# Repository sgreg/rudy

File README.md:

# RUDY - the Random USB Device

RUDY started out as a test and play-around device for USB development using the [Objective Development V-USB library](https://www.obdev.at/products/vusb/index.html), but also serves as standard ATmega328 development board.

## Links
- [Official Website](https://rudy.craplab.fi/)
- [Hackaday.io Project Page](https://hackaday.io/project/174101-rudy)

## Features

- breadboard-friendly prototyping board, taking up only one additional row on each side compared to a standalone ATmega328 microcontroller
- Arduino compatible [..ish](firmware/arduino/)
- USB port wired to the ATmega328 for out-of-the-box USB functionality via the V-USB library
- own, dedicated [USB VID/PID pair](http://pid.codes/1209/B00B/) thanks to [pid.codes](http://pid.codes/)
- USB-powered with additional 3.3V voltage regulator on board to select either 5.0 or 3.3V supply voltage
- clocked by 12.0 MHz crystal to comply with V-USB and also 3.3V supply voltage
- 6-pin ISP header for programming, with additional option to power the board directly from the programmer
- power-indicating LEDs mounted under the IC, shining in a mysterious glow (oh yeah)
- DIP28 ATmega328, allowing easy replacement if it ever gets fried (no no)
- fully open source and [certified as such](https://certification.oshwa.org/fi000002.html) by the [Open Source Hardware Association (OSHWA)](https://www.oshwa.org/)

<p align="center">

</p>

## Hardware

RUDY is primarily a hardware project, so all the design file for KiCad along with the schematic as PDF and Gerber files are found in the [`hardware/`](hardware/rudy/) directory. And if you want to go straight ahead and build your own board, [the PCB is available from OSH Park](https://oshpark.com/projects/RQf8bXd4).

As RUDY can theoretically function as an [USBasp programmer](https://www.fischl.de/usbasp/), there's also [an adapter board](hardware/usbasp-adapter) available - and is also [available from OSH Park](https://oshpark.com/projects/pueZ0qkO)

## Firmware

Again, RUDY is primarily a development board, and as such is there for _your_ firmware. But well, everything and everyone has to start somewhere, so the [`firmware/`](firmware/) directory has a (still-to-grow) collection of example projects, both using the V-USB library and using RUDY as regular, ATmega328 microcontroller board.

## License
RUDY is fully open source. All hardware files are released under the [CERN Open Hardware License v1.2](https://ohwr.org/project/licenses/wikis/cern-ohl-v1.2), all example source code is released under the [MIT License](https://choosealicense.com/licenses/mit/), and all documentation within this git repository is provided under the terms of a [Creative Commons Attribution 4.0 International (CC BY 4.0) license](https://creativecommons.org/licenses/by/4.0/).

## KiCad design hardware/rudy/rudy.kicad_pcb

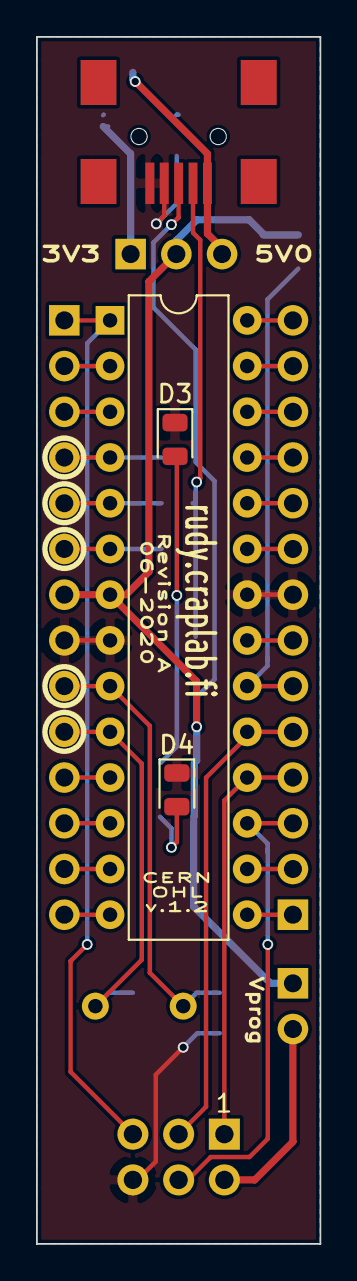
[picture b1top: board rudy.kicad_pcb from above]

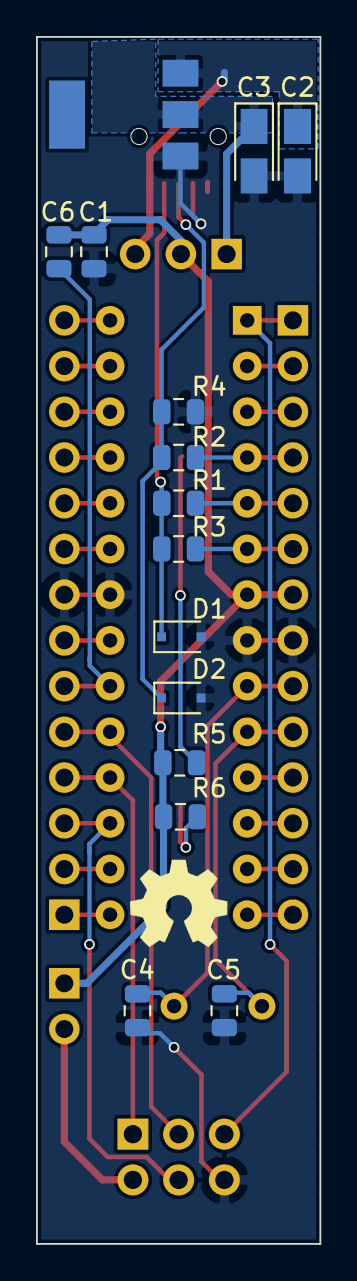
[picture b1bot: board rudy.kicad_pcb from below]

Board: 2 copper layers, 15.7 x 67.1 mm, 26 parts (16 on the bottom side), 34 nets.

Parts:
C1, C6: 100n; C_0805_2012Metric
C2, C3: 10u; CP_Tantalum_Case-A_EIA-3216-18_Reflow
C4, C5: 22p; C_0805_2012Metric
D1, D2: 3V6; D_SOD-323F
D3, D4: LED; LED_0805_2012Metric
IC1: ATMEGA328-P; DIP-28_W7.62mm
JP1: JUMPER3; Pin_Header_Straight_1x03_Pitch2.54mm
JP2: JUMPER; Pin_Header_Straight_1x02_Pitch2.54mm
P1: CONN1; Socket_Strip_Straight_1x14_Pitch2.54mm
P2: CONN2; Socket_Strip_Straight_1x14_Pitch2.54mm
P3: SERPROG; IDC_Header_Straight_6pins
P4: USB_B; USB_Mini-B
R1, R2: 68R; R_0805_2012Metric
R3: 1k5; R_0805_2012Metric
R4: 1M; R_0805_2012Metric
R5, R6: 120R; R_0805_2012Metric
U1: LD1117S33TR; SOT-223
Y1: Crystal; Crystal_HC49-U_Vertical
oshw: LOGO; oshw_50

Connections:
/#RESET: IC1.1, P1.1, P3.5
/AREF: IC1.21, P2.7
/AVCC: C6.2, IC1.20, P2.6
/PB0: IC1.14, P1.14
/PB1: IC1.15, P2.1
/PB2: IC1.16, P2.2
/PB3: IC1.17, P2.3, P3.4
/PB4: IC1.18, P2.4, P3.1
/PB5: IC1.19, P2.5, P3.3
/PB6: C4.1, IC1.9, P1.9, Y1.1
/PB7: C5.1, IC1.10, P1.10, Y1.2
/PC0: IC1.23, P2.9
/PC1: IC1.24, P2.10
/PC2: IC1.25, P2.11
/PC3: IC1.26, P2.12
/PC4: IC1.27, P2.13
/PC5: IC1.28, P2.14
/PD0: IC1.2, P1.2
/PD1: IC1.3, P1.3
/PD2: IC1.4, P1.4, R2.1
/PD3: IC1.5, P1.5, R1.1
/PD4: IC1.6, P1.6, R3.1
/PD5: IC1.11, P1.11
/PD6: IC1.12, P1.12
/PD7: IC1.13, P1.13
/VCC: C1.1, C6.1, IC1.7, JP1.2, JP2.1, P1.7, R5.2, R6.2
GND: C1.2, C2.2, C3.2, C4.2, C5.2, D1.2, D2.2, D3.1, D4.1, IC1.8, IC1.22, P1.8, P2.8, P3.6, P4.4, P4.5, R4.2, U1.1
unnamed: C2.1, JP1.3, P4.1, U1.3
unnamed: C3.1, JP1.1, U1.2
unnamed: D1.1, P4.2, R1.2, R3.2
unnamed: D2.1, P4.3, R2.2, R4.1
unnamed: D3.2, R5.1
unnamed: D4.2, R6.1
unnamed: JP2.2, P3.2

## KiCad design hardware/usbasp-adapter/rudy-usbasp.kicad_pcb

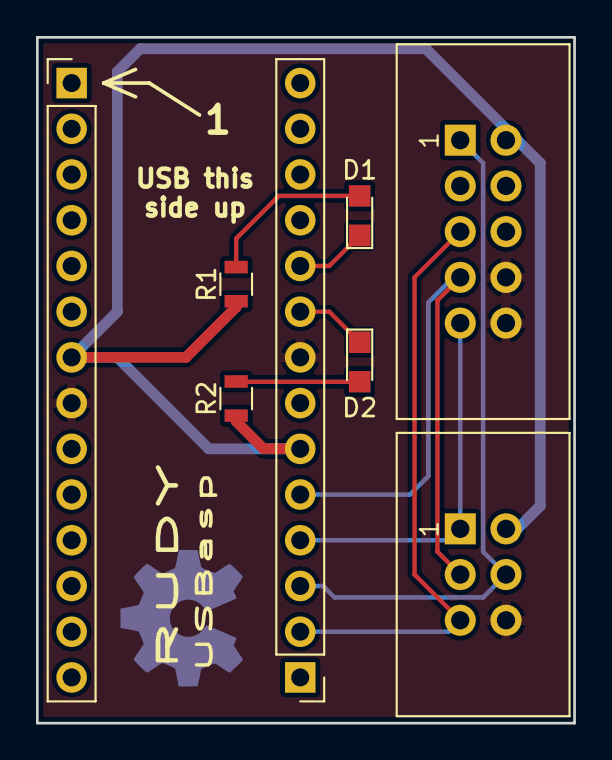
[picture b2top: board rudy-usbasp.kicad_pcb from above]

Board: 2 copper layers, 29.8 x 38.1 mm, 8 parts (0 on the bottom side), 10 nets.

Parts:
D1, D2: LED; LED_0805
J1, J2: CONN_01X14; Pin_Header_Straight_1x14_Pitch2.54mm
J3: ISP 6pin; IDC_Header_Straight_6pins
J4: ISP 10pin; IDC_Header_Straight_10pins
R1, R2: 120; R_0805

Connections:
/MISO: J2.4, J3.1, J4.9
/MOSI: J2.3, J3.4, J4.1
/RESET: J2.2, J3.5, J4.5
/SCK: J2.5, J3.3, J4.7
GND: J1.8, J2.8, J3.6, J4.8, J4.10
unnamed: D1.1, J2.10
unnamed: D1.2, R1.2
unnamed: D2.1, J2.9
unnamed: D2.2, R2.2
VCC: J1.7, J2.6, J3.2, J4.2, R1.1, R2.1

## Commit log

2017-07-23 Hardware Revision A
    Added full KiCad project with schematic (plus PDF), PCB design, net list
    and BOM, plus KiCad project itself, of Revision A hardware.
2017-07-23 Added Gerber files for hardware Revision A
2017-07-24 Added common firmware files and Hello USB example
    All initial common files, including the V-USB library itself and a
    generic Makefile, along with a simple Hello USB dummy device.
2017-07-24 Added firmware related .gitignore entries
    And getting rid of accidentally commited vim .swp files..
2017-08-03 Add license file
    Adding license file for software: GPL
    Adding license files for hardware: CERN OHL
2017-08-09 Hardware revision A adjustments
    Second iteration, changing SMD footprints from hand solder types to
    normal / reflow types. Re-arranging power selector and re-routing
    everything, fixing some minor general things along the way.
    Changed Zener diode / resistor order for USB D+/D- lines.
    Added solder paste layer Gerber file.
2017-08-09 Changed USB port config to match actual hardware
    Previous port assignments were based on 4chord MIDI hardware. Now real
    RUDY hardware has arrived, which uses different pins, need to adjust it.
    Also added RUDY's own dedicated USB VID/PID pair, courtesy of pid.codes
    and InterBiometrics.
2017-08-09 Update for latest KiCAD version
    Never updated the KiCAD ppa after last dist upgrade, so been using old
    version ever since, now updated and had to adjust one component.
    Changed Gerber file extension format along the way.
2017-08-21 Changed Zener diodes
    Changed footprint for D1 and D2 Zener diodes from Mini MILF to SOD-323F
    and moved their position in front of R1 and R2.
    That came with a bit of rerouting, and trying to keep the pad position
    close enough to the initial ones, so I don't have to order new stencils
    right away (while even still waiting for them)
2017-09-12 Fixed USB-B component after KiCad update
    Turns out 1-3-2-4-5 is a more logical pin arrangement for some people,
    and I fucked up paying attention to this, so D+ and D- USB lines got
    swapped in the schematic component. Should have been more suspicious
    why I had to do so much re-routing after updating the Zener diodes.
2017-09-20 Updated README to current state and added new items
    First prototypes got soldered and new ideas (USBasp) came up.
2017-09-20 USBasp adapter board hardware added
    Simple adapter board with a 6pin and 10pin IDC connector, LEDs and
    resistors for power / connection indication (handled by USBasp firmware)
    and two female 14pin headers to dock RUDY into.
    When RUDY is programmed with USBasp firmware, it can act as fully
    functional USBasp programmer with this board.
2017-09-20 Some gitignore adjustments
    Keep cache lib for KiCad schematics and fix some wildcards
2020-07-21 HW: added LEDs and AVCC cap
    There were no LEDs.
    Why were there no LEDs?!
    Everything needs LEDs!
    So now there are, indicating that the device is actually powered, which
    will lessen occasional confusion about that (especially when one forgets
    to adjust the jumper after flashing).
2020-07-21 FW: moved examples and refactored V-USB config override handling
    V-USB is great, but even though this is specifically a Random *USB*
    Device, it doesn't have to be, and using V-USB functionality is really
    more optional, and is therefore now separated.
    Not that there's much to separate it from, but now it's easier to add
    bare metal examples in the future.
    While moving the examples, the config handling for V-USB was refactored
2020-07-22 FW: split include directories in Makefile and add asm target
    To easier add includes in project-specific Makefile, the `-I` parameters
    were seperated from the `CFLAGS` variable and put in its own `INCLUDES`
    variable.
    Also added generic asm target for all .S files.
2020-07-22 FW: USB interrupt-in endpoints are project-specific now
    `USB_CFG_HAVE_INTRIN_ENDPOINT`/`3` values are not hardcoded anymore but
    defined in the usbconfig-rudy.h by each project now.
2020-07-24 FW: usbconfig settings moved to override file
    More settings moved: `USB_CFG_INTR_POLL_INTERVAL` for setting the
    interrupt polling interval, and `USB_CFG_HID_REPORT_DESCRIPTOR_LENGTH`
    for HID devices.
    Also removed some old leftover parts from the previous override way
2020-07-27 FW: Added script to check if all required tools are installed
    To make life easier, check-system.sh is going to check if the required
    tools (make, GCC, libc, binutils, AVRDUDE) are installed on the system
    and tells if some are missing. On .deb or Red Hat systems, it also
    offers to install missing packages right away.
    If all packages are installed, it compiles a little dummy C file to
    verify that it really all works.
2020-07-27 FW: Added programmer.mk to tell AVRDUDE what programmer to use
    By default this is all tested and set up to work with USBasp, but not
    everyone might use USBasp as programmer. To make it easier to change the
    programmer AVRDUDE will use, firwmare/programmer.mk is introduced and
    the common.mk Makefile will use that.
2020-07-28 FW: updated / improved documentation for V-UB Hello USB example
2020-07-28 FW: Added bare metal Blinky example and common files
    Initial build environment and first example for bare metal usage of RUDY
2020-07-28 FW: improved V-USB common files README
2020-07-28 FW: Added general information and instructions about firmware
    README with general info on the firmware files, build instructions,
    flashing instructions, powering up, installing dependencies, etc.
2020-07-28 Updated main README
    RUDY is going forward, time to update the README and add the current
    state and what's going on here.
2020-07-28 FW: Added general README for V-USB examples
2020-07-28 FW: Added V-USB Example 02: USB LED
    Control an LED via USB. Allows to turn the an LED connected to port PD5
    to be turned on, off, or set to a specific PWM value via USB.
    Includes a Python script to communicate with the device.
2020-07-28 FW: use correct binutils package for Debian in check-system script
    Like avr-gcc / gcc-avr, it's the same with avr-binutils / binutils-avr,
    which wasn't handled properly. Now it is, and since there's plenty of
    checking /etc/*release now, the script just determines the distro right
    away in the beginning.
    Also, this must be actual bash script, not sh, as it uses bash-specific
    stuff like += operator (fails at Raspberry Pi for example)
2020-07-29 FW: Added udev section for V-USB to README
2020-07-29 Bunch of README fixes
    Some typo here, some wrong word there. Also missed the part about having
    its own USB VID/PID pair. And there was a section prepared to build the
    firmware via Docker, but decided against that for now - kinda doesn't
    make much sense if AVR toolchains are more or less available out of the
    box in most cases.
2020-07-29 FW: Added V-USB Example 03: Caesar Cipher
    Send messages to the device and receive it back shifted with the Caesar
    Cipher of a given amount of places.
    Includes also a Python script to communicate with the device
2020-07-29 FW: Added V-USB Example 04: MIDI
    Turn RUDY into a USB MIDI device and connect a sensor to its ADC to
    create the MIDI notes in the first place
2020-07-30 FW: Added V-USB Example 05: HID Mouse (taken from V-USB itself)
    HID mouse that just draws a circle, taken from the V-USB examples
2020-07-30 Scaled down images
    Kinda no point to have huge images here, smaller ones will do just fine
2020-07-30 FW: Added V-USB Example 06: USBasp
    Ported USBasp itself to run on RUDY
2020-08-01 FW: Added Arduino information
2020-08-01 FW: Added arduino/ firmware folder to README
2020-08-01 FW: Found a missing link in a README
2020-08-01 FW: Added Arduino Example 01: Blinky
    It's just the usual blinking LED example, but adjusted for RUDY, which
    expects an external LED connected to Digital Pin 5 / pin 11
2020-08-01 Added links to website and Hackaday.io page
2020-08-04 Don't feel too blue my RUDY
    White balance somewhat corrected on the main picture
2020-08-04 Bunch o' words rearranged
2020-08-06 Added documentation license informatione to README
2020-08-07 Added OSHWA Certification Mark
    Oh, hi Mark!
